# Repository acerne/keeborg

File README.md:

# Keeborg
*Oh look, another split keyboard*	

## Idea
Keeborg is a sandbox prototype inspired from split keyboards like ErgoDox, Iris, Sol2 and many others, that give your tumbs more to do besides spacebar mashing. Taking a level further with thoughts of rotary encoders, joysticks, trackballs and other input devices, rarely seen o na keyboard.

## Status
Designed a simple one-sided reversible PCB, made a fully functional thumb-less left-hand cluster. Had header connectors for some modular miny-pcb addons. After some testing decided it's not as expected and abandoned the project.

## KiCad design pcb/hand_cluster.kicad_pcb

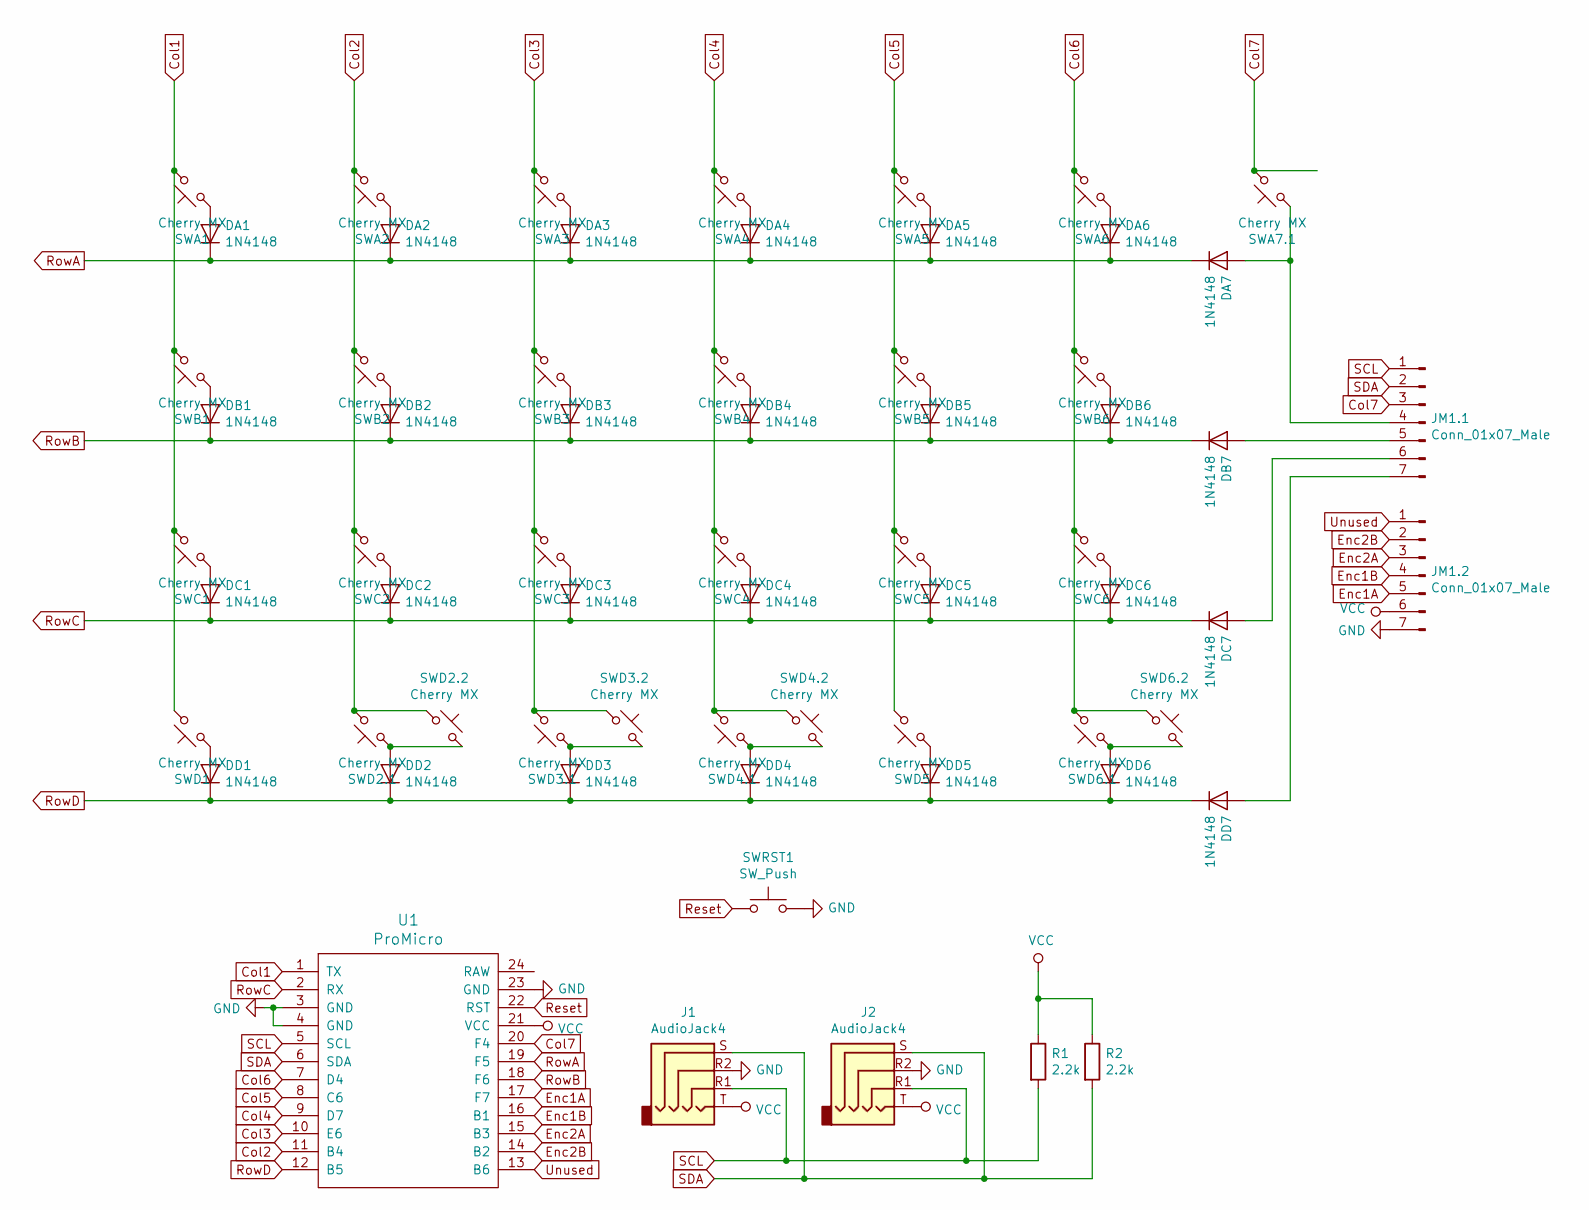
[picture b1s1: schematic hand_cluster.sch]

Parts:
DA1, DA2, DA3, DA4, DA5, DA6, DA7: 1N4148; D_DO-35_SOD27_P7.62mm_Horizontal
DB1, DB2, DB3, DB4, DB5, DB6, DB7: 1N4148; D_DO-35_SOD27_P7.62mm_Horizontal
DC1, DC2, DC3, DC4, DC5, DC6, DC7: 1N4148; D_DO-35_SOD27_P7.62mm_Horizontal
DD1, DD2, DD3, DD4, DD5, DD6, DD7: 1N4148; D_DO-35_SOD27_P7.62mm_Horizontal
J1, J2: AudioJack4; TRRS-PJ-320A-dual-labeled
JM1.1, JM1.2: Conn_01x07_Male; PinHeader_1x07_P2.54mm_Vertical
R1, R2: 2.2k; Resistor
SWA1: Cherry MX; Hybrid_Plate_150H_Dual_hole-nosilk
SWA2, SWA3, SWA4, SWA5, SWA6, SWA7.1: Cherry MX; Hybrid_Plate_100H_Dual_hole-nosilk
SWB1: Cherry MX; Hybrid_Plate_150H_Dual_hole-nosilk
SWB2, SWB3, SWB4, SWB5, SWB6: Cherry MX; Hybrid_Plate_100H_Dual_hole-nosilk
SWC1: Cherry MX; Hybrid_Plate_150H_Dual_hole-nosilk
SWC2, SWC3, SWC4, SWC5, SWC6: Cherry MX; Hybrid_Plate_100H_Dual_hole-nosilk
SWD1: Cherry MX; Hybrid_Plate_150H_Dual_hole-nosilk
SWD2.1, SWD2.2, SWD3.1, SWD3.2, SWD4.1, SWD4.2, SWD5, SWD6.1, SWD6.2: Cherry MX; Hybrid_Plate_100H_Dual_hole-nosilk
SWRST1: SW_Push; SW_PUSH_6mm
U1: ProMicro; ArduinoProMicro

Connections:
Ard10_Analog: JM1.2.1, U1.13 (B6)
Ard14_MISO: JM1.2.3, U1.15 (B3)
Ard15_SCLK: JM1.2.4, U1.16 (B1)
Ard16_MOSI: JM1.2.2, U1.14 (B2)
Ard18_Analog: JM1.2.5, U1.17 (F7)
Col1: SWA1.2, SWB1.2, SWC1.2, SWD1.2, U1.1 (TX)
Col2: SWA2.2, SWB2.2, SWC2.2, SWD2.1.2, SWD2.2.1, U1.11 (B4)
Col3: SWA3.2, SWB3.2, SWC3.2, SWD3.1.2, SWD3.2.1, U1.10 (E6)
Col4: SWA4.2, SWB4.2, SWC4.2, SWD4.1.2, SWD4.2.1, U1.9 (D7)
Col5: SWA5.2, SWB5.2, SWC5.2, SWD5.2, U1.8 (C6)
Col6: SWA6.2, SWB6.2, SWC6.2, SWD6.1.2, SWD6.2.1, U1.7 (D4)
Col7: JM1.1.3, SWA7.1.2, U1.20 (F4)
GND: J1.R2, J2.R2, JM1.2.7, SWRST1.2, U1.3 (GND), U1.4 (GND), U1.23 (GND)
unnamed: DA1.2 (A), SWA1.1
unnamed: DA2.2 (A), SWA2.1
unnamed: DA3.2 (A), SWA3.1
unnamed: DA4.2 (A), SWA4.1
unnamed: DA5.2 (A), SWA5.1
unnamed: DA6.2 (A), SWA6.1
unnamed: DA7.2 (A), JM1.1.4, SWA7.1.1
unnamed: DB1.2 (A), SWB1.1
unnamed: DB2.2 (A), SWB2.1
unnamed: DB3.2 (A), SWB3.1
unnamed: DB4.2 (A), SWB4.1
unnamed: DB5.2 (A), SWB5.1
unnamed: DB6.2 (A), SWB6.1
unnamed: DB7.2 (A), JM1.1.5
unnamed: DC1.2 (A), SWC1.1
unnamed: DC2.2 (A), SWC2.1
unnamed: DC3.2 (A), SWC3.1
unnamed: DC4.2 (A), SWC4.1
unnamed: DC5.2 (A), SWC5.1
unnamed: DC6.2 (A), SWC6.1
unnamed: DC7.2 (A), JM1.1.6
unnamed: DD1.2 (A), SWD1.1
unnamed: DD2.2 (A), SWD2.1.1, SWD2.2.2
unnamed: DD3.2 (A), SWD3.1.1, SWD3.2.2
unnamed: DD4.2 (A), SWD4.1.1, SWD4.2.2
unnamed: DD5.2 (A), SWD5.1
unnamed: DD6.2 (A), SWD6.1.1, SWD6.2.2
unnamed: DD7.2 (A), JM1.1.7
Reset: SWRST1.1, U1.22 (RST)
RowA: DA1.1 (K), DA2.1 (K), DA3.1 (K), DA4.1 (K), DA5.1 (K), DA6.1 (K), DA7.1 (K), U1.19 (F5)
RowB: DB1.1 (K), DB2.1 (K), DB3.1 (K), DB4.1 (K), DB5.1 (K), DB6.1 (K), DB7.1 (K), U1.18 (F6)
RowC: DC1.1 (K), DC2.1 (K), DC3.1 (K), DC4.1 (K), DC5.1 (K), DC6.1 (K), DC7.1 (K), U1.2 (RX)
RowD: DD1.1 (K), DD2.1 (K), DD3.1 (K), DD4.1 (K), DD5.1 (K), DD6.1 (K), DD7.1 (K), U1.12 (B5)
SCL: J1.R1, J2.R1, JM1.1.1, R1.2, U1.5 (SCL)
SDA: J1.S, J2.S, JM1.1.2, R2.2, U1.6 (SDA)
VCC: J1.T, J2.T, JM1.2.6, R1.1, R2.1, U1.21 (VCC)

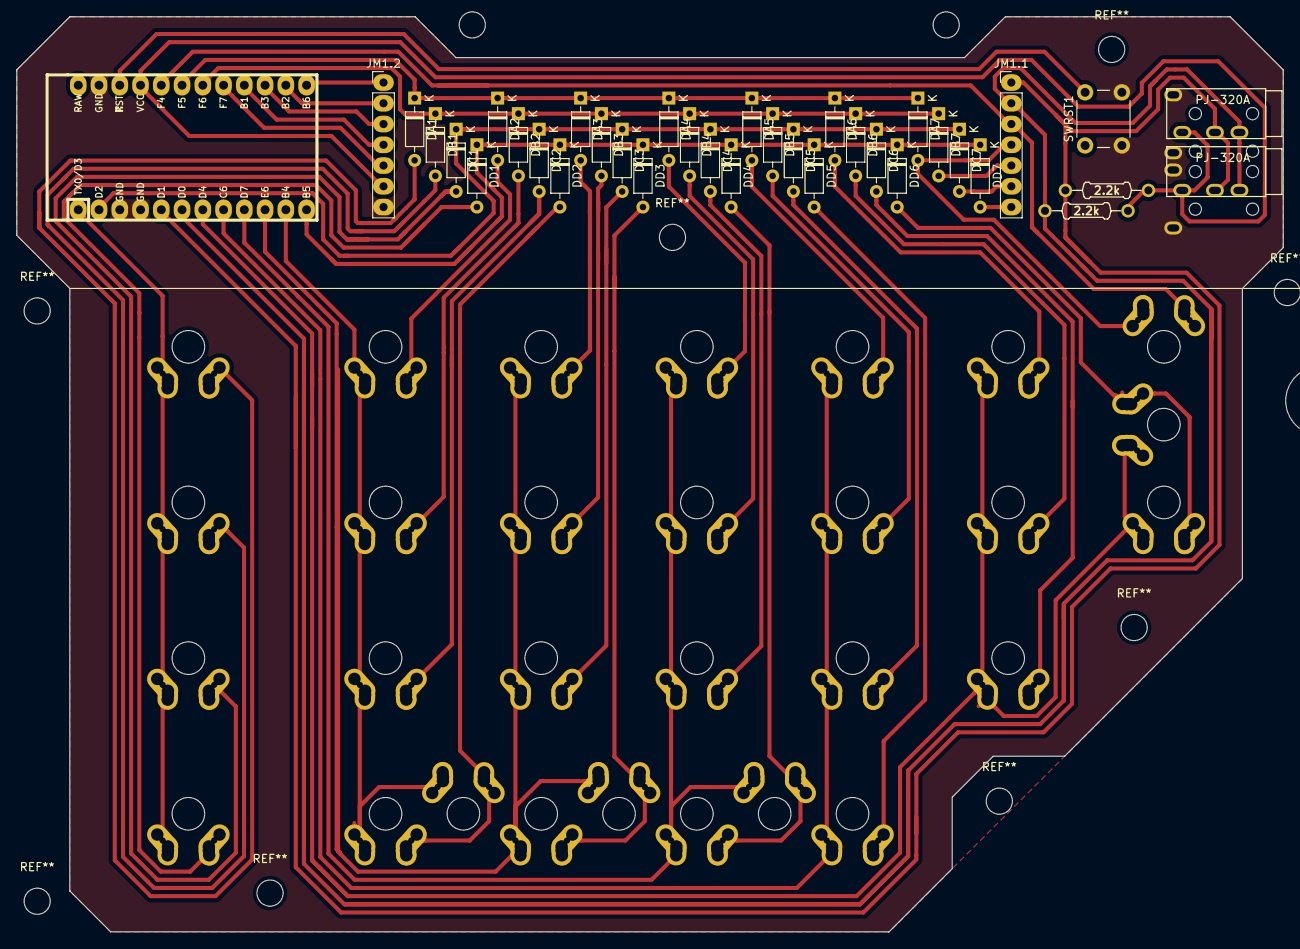
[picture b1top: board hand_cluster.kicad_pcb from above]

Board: 2 copper layers, 155.0 x 112.0 mm, 65 parts (0 on the bottom side), 49 nets.

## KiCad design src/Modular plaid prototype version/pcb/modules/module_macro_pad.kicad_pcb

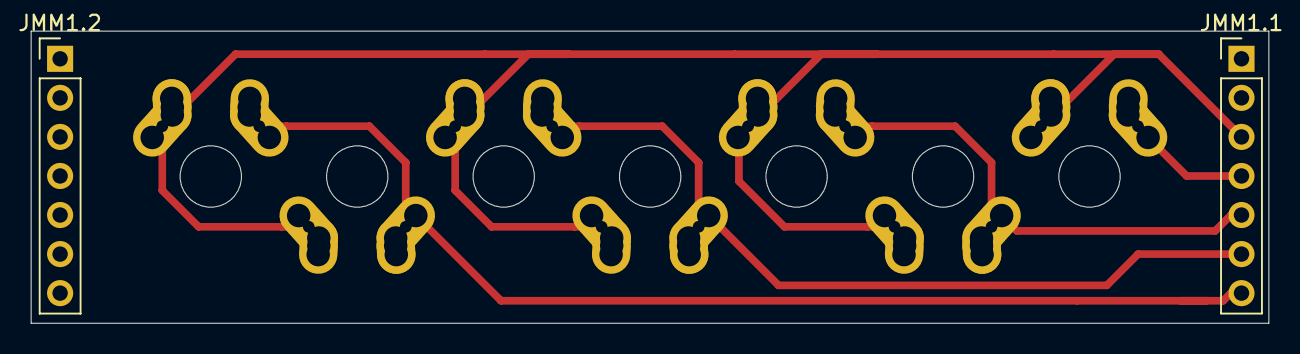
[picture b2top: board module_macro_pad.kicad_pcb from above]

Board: 2 copper layers, 80.5 x 19.0 mm, 9 parts (0 on the bottom side), 5 nets.

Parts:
JMM1.1: :Conn_01x07_Female; PinHeader_1x07_P2.54mm_Vertical
JMM1.2: Conn_01x07_Female; PinHeader_1x07_P2.54mm_Vertical
SWA7.2: SW_Push_45deg; Hybrid_Plate_100H_Dual_hole-nosilk
SWB7.1, SWB7.2: SW_Push_45deg; Hybrid_Plate_100H_Dual_hole-nosilk
SWC7.1, SWC7.2: SW_Push_45deg; Hybrid_Plate_100H_Dual_hole-nosilk
SWD7.1, SWD7.2: SW_Push_45deg; Hybrid_Plate_100H_Dual_hole-nosilk

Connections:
unnamed: JMM1.1.3, SWA7.2.1, SWB7.1.1, SWB7.2.2, SWC7.1.1, SWC7.2.2, SWD7.1.1, SWD7.2.2
unnamed: JMM1.1.4, SWA7.2.2
unnamed: JMM1.1.5, SWB7.1.2, SWB7.2.1
unnamed: JMM1.1.6, SWC7.1.2, SWC7.2.1
unnamed: JMM1.1.7, SWD7.1.2, SWD7.2.1

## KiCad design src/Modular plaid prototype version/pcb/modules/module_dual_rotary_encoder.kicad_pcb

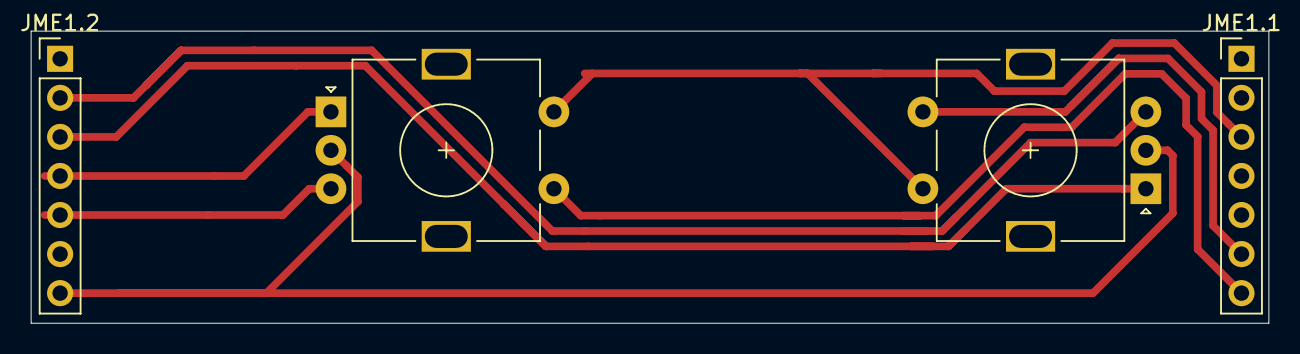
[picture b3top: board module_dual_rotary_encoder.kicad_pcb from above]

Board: 2 copper layers, 80.5 x 19.0 mm, 4 parts (0 on the bottom side), 8 nets.

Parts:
ESW1, ESW2: Rotary_Encoder_Switch; RotaryEncoder_EC11
JME1.1: Conn_01x7_Female; PinHeader_1x07_P2.54mm_Vertical
JME1.2: Conn_01x07_Female; PinHeader_1x07_P2.54mm_Vertical

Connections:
unnamed: ESW1.A, JME1.2.4
unnamed: ESW1.B, JME1.2.5
unnamed: ESW1.C, ESW2.C, JME1.2.7
unnamed: ESW1.S1, JME1.1.7
unnamed: ESW1.S2, ESW2.S2, JME1.1.3
unnamed: ESW2.A, JME1.2.3
unnamed: ESW2.B, JME1.2.2
unnamed: ESW2.S1, JME1.1.6

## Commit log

2019-09-21 Added key layout files
2019-09-21 Added the initial sandwich case design
2019-09-21 Updated the case design, merged everything into a single file
2019-09-25 Modified switchplate to square switch cutouts
2019-09-26 Started working on schematics
2019-09-27 Added excusions for unnecessary KiCad files
2019-09-27 Included another KiCad library as submodule
2019-09-27 Renamed pcb files, added two encoders to schematics
2019-09-27 Deleted untracked pcb files
2019-09-27 Updated the layout; added a key to each side
2019-09-27 Replaced a keyboard part library
2019-09-27 Linked components with pcb footprints
2019-10-04 Designed the version of a plaid modular hand cluster
2019-10-04 Designed macropad and rotary encoder extension modules
2019-10-04 Forgot to commit a file
2019-10-17 Upadeted modular pcb project and moved them to modules folder
2019-10-17 Modified the main pcb hand cluster to a near completed prototype design
2019-10-17 Added some customized footprints
2019-10-17 Moved files to different design folders
2019-10-17 Added some images
2020-07-31 Updated status
2020-08-25 Aded photos
2020-08-25 Added photos to readme
